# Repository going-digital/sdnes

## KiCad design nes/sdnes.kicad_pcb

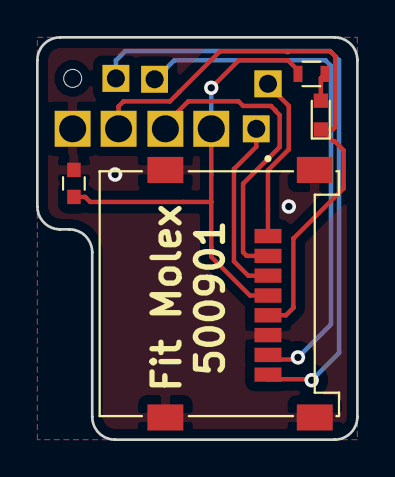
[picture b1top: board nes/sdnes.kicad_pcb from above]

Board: 2 copper layers, 17.8 x 22.4 mm, 5 parts (0 on the bottom side), 9 nets.

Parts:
C2: C_Small; C_0603
D2: Red LED; LED_0603
J2: 500901-0801; MOLEX_500901-0801
R2: 1K; R_0603
SK2: nesclassic:Testpoint_cluster; FTM-NES-SD-pads

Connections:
/0V: C2.2, J2.6, J2.SH1, J2.SH2, J2.SH3, J2.SH4, SK2.6
/3V: C2.1, J2.4, R2.1, SK2.4
/CLK: D2.1, J2.5, SK2.5
/CMD: J2.3, SK2.3
/D0: J2.7, SK2.7
/D1: J2.8, SK2.8
/D2: J2.1, SK2.1
/D3: J2.2, SK2.2
unnamed: D2.2, R2.2

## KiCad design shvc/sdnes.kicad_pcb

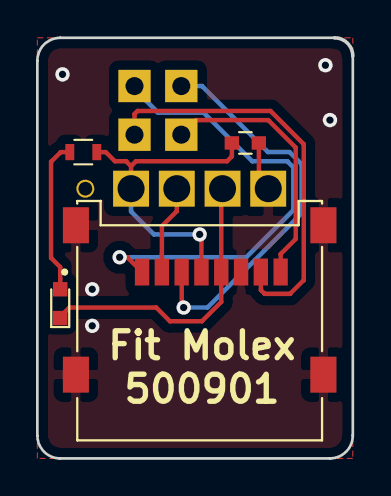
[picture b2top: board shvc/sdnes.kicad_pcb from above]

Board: 2 copper layers, 17.5 x 23.3 mm, 5 parts (0 on the bottom side), 9 nets.

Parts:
C1: C_Small; C_0603
D1: Red LED; LED_0603
J1: 500901-0801; MOLEX_500901-0801
R1: 1K; R_0603
SK1: Testpoint_cluster; FTM-SHVC-SD-pads

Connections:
/0V: C1.2, J1.6, J1.SH1, J1.SH2, J1.SH3, J1.SH4, SK1.6
/3V: C1.1, J1.4, R1.1, SK1.4
/CLK: D1.1, J1.5, SK1.5
/CMD: J1.3, SK1.3
/D0: J1.7, SK1.7
/D1: J1.8, SK1.8
/D2: J1.1, SK1.1
/D3: J1.2, SK1.2
unnamed: D1.2, R1.2

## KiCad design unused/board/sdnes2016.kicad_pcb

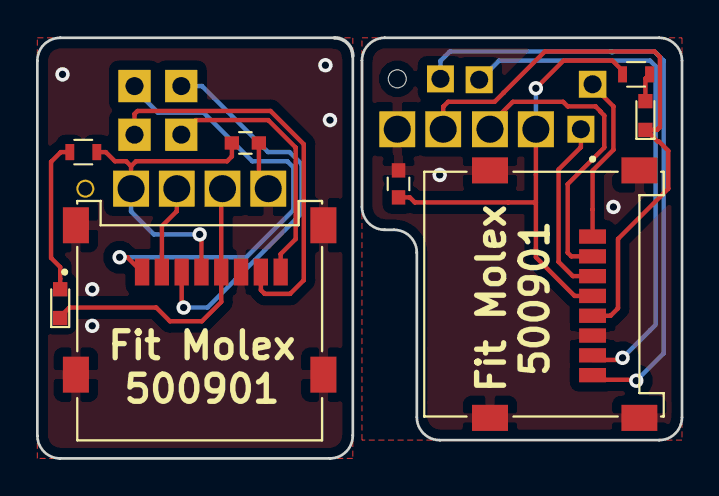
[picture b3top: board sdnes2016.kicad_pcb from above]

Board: 2 copper layers, 35.8 x 23.3 mm, 10 parts (0 on the bottom side), 18 nets.

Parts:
C1, C2: C_Small; C_0603
D1, D2: Red LED; LED_0603
J1, J2: 500901-0801; MOLEX_500901-0801
R1, R2: 1K; R_0603
SK1: Testpoint_cluster; FTM-SHVC-SD-pads
SK2: Testpoint_cluster; FTM-NES-SD-pads

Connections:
/0V: C1.2, J1.6, J1.SH1, J1.SH2, J1.SH3, J1.SH4, SK1.6
/0Vb: C2.2, J2.6, J2.SH1, J2.SH2, J2.SH3, J2.SH4, SK2.6
/3V: C1.1, J1.4, R1.1, SK1.4
/3Vb: C2.1, J2.4, R2.1, SK2.4
/CLK: D1.1, J1.5, SK1.5
/CLKb: D2.1, J2.5, SK2.5
/CMD: J1.3, SK1.3
/CMDb: J2.3, SK2.3
/D0: J1.7, SK1.7
/D0b: J2.7, SK2.7
/D1: J1.8, SK1.8
/D1b: J2.8, SK2.8
/D2: J1.1, SK1.1
/D2b: J2.1, SK2.1
/D3: J1.2, SK1.2
/D3b: J2.2, SK2.2
unnamed: D1.2, R1.2
unnamed: D2.2, R2.2

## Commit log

2018-08-23 First attempt
2018-08-23 nessd to sdnes
2018-08-23 Fix json
2018-08-23 Strip back
2018-08-23 Add soldermask and vias def
2018-08-23 tidy
2018-08-23 Add SD socket
2018-08-23 Fixes
2018-08-23 Correct pad coords
2018-08-23 Additional pads
2018-08-23 Fix G4 position
2018-08-23 Round off pads
2018-08-23 Add SMDs
2018-08-23 Add placeholder external pads
2018-08-23 Flip pads
2018-08-23 Arrange components
2018-08-23 Rearrange components
2018-08-23 Simplify board outline
2018-08-23 Move from castellated to normal plated holes
2018-08-23 Fix errant comma
2018-08-23 Footprint tweak
2018-08-23 Recentre pads
2018-08-23 Layout tweaks
2018-08-24 Mirror SD socket
2018-08-24 shuffle components
2018-08-24 Add routing
2018-08-24 Location tweaks
2018-08-24 Position tweaks
2018-09-23 Functional design in Kicad
2018-09-23 Fix silkscreen
2018-09-23 Add readme
2018-09-23 Add Gerbers for manufacture
2018-09-23 Ignore gerber and drill files
2018-09-23 Expanded Readme, added license
2018-09-23 Mention KiCad
2018-09-23 Artwork graphics
2018-09-23 Add images
2018-09-23 Add links to fabrication files.
2018-09-26 Fix silkscreen
    Fixes issue 1
2018-09-26 Revert "Fix silkscreen"
    This reverts commit b91a6601b2e49d2b5b00c3b97c6f2e9545f83911.
2021-11-09 Update readme.md
    https://forum.kicad.info/t/warning-avoid-all-links-to-kicad-pcb-org-use-kicad-org/31521
